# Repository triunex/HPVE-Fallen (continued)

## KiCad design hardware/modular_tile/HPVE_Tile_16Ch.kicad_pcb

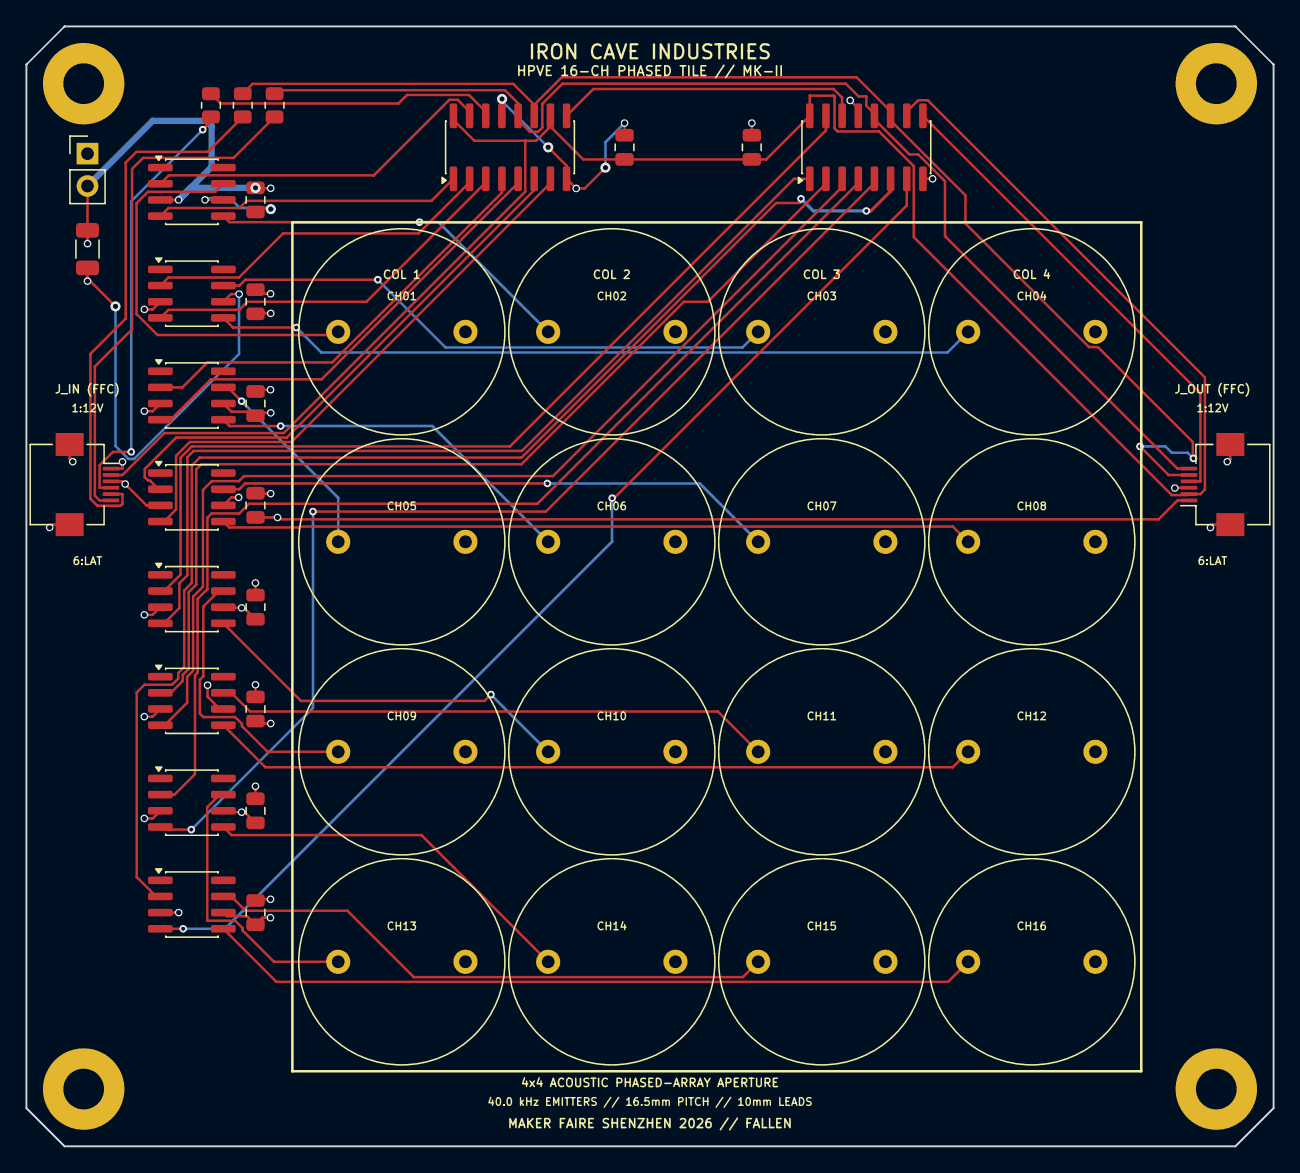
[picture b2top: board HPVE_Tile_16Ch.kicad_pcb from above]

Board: 4 copper layers, 98.0 x 88.0 mm, 47 parts (0 on the bottom side), 43 nets.

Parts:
C1, C2: 0.1uF; C_0805_2012Metric
C101, C102, C103, C104, C105, C106, C107, C108: 0.1uF_50V; C_0805_2012Metric
C_BULK: 10uF_25V; C_1206_3216Metric
H1, H2, H3, H4: M3_Pad; MountingHole_3.2mm_M3_Pad
J_IN: 0.5mm_FFC_6P; Hirose_FH12-6S-0.5SH_1x06-1MP_P0.50mm_Horizontal
J_OUT: 0.5mm_FFC_6P; Hirose_FH12-6S-0.5SH_1x06-1MP_P0.50mm_Horizontal
J_PWR: AUX_12V_IN; PinHeader_1x02_P2.54mm_Vertical
R1, R2, R3: 33R; R_0805_2012Metric
TX1, TX2, TX3, TX4, TX5, TX6, TX7, TX8, TX9, TX10, TX11, TX12, TX13, TX14, TX15, TX16: 400ST160_FEMALE_SOCKET; TX_400ST160_P10.0mm
U1, U2: 74HC595; SOIC-16_3.9x9.9mm_P1.27mm
U101, U102, U103, U104, U105, U106, U107, U108: TC4427ACOA; SOIC-8_3.9x4.9mm_P1.27mm

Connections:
+5V: C1.1, C2.1, J_IN.2, J_OUT.2, U1.10, U1.16, U2.10, U2.16
+12V: C101.1, C102.1, C103.1, C104.1, C105.1, C106.1, C107.1, C108.1, C_BULK.1, J_IN.1, J_OUT.1, J_PWR.1, U101.6, U102.6, U103.6, U104.6, U105.6, U106.6, U107.6, U108.6
DRV_1: TX1.1, U101.7
DRV_2: TX2.1, U101.5
DRV_3: TX3.1, U102.7
DRV_4: TX4.1, U102.5
DRV_5: TX5.1, U103.7
DRV_6: TX6.1, U103.5
DRV_7: TX7.1, U104.7
DRV_8: TX8.1, U104.5
DRV_9: TX9.1, U105.7
DRV_10: TX10.1, U105.5
DRV_11: TX11.1, U106.7
DRV_12: TX12.1, U106.5
DRV_13: TX13.1, U107.7
DRV_14: TX14.1, U107.5
DRV_15: TX15.1, U108.7
DRV_16: TX16.1, U108.5
GND: C1.2, C2.2, C101.2, C102.2, C103.2, C104.2, C105.2, C106.2, C107.2, C108.2, C_BULK.2, H1.1, H2.1, H3.1, H4.1, J_IN.3, J_IN.MP, J_OUT.3, J_OUT.MP, J_PWR.2, TX1.2, TX2.2, TX3.2, TX4.2, TX5.2, TX6.2, TX7.2, TX8.2, TX9.2, TX10.2, TX11.2, TX12.2, TX13.2, TX14.2, TX15.2, TX16.2, U1.8, U1.13, U2.8, U2.13, U101.3, U102.3, U103.3, U104.3, U105.3, U106.3, U107.3, U108.3
SIG_1: U1.15, U101.2
SIG_2: U1.1, U101.4
SIG_3: U1.2, U102.2
SIG_4: U1.3, U102.4
SIG_5: U1.4, U103.2
SIG_6: U1.5, U103.4
SIG_7: U1.6, U104.2
SIG_8: U1.7, U104.4
SIG_9: U2.15, U105.2
SIG_10: U2.1, U105.4
SIG_11: U2.2, U106.2
SIG_12: U2.3, U106.4
SIG_13: U2.4, U107.2
SIG_14: U2.5, U107.4
SIG_15: U2.6, U108.2
SIG_16: U2.7, U108.4
SPI_LATCH: J_OUT.6, R3.2, U1.12, U2.12
SPI_LATCH_IN: J_IN.6, R3.1
SPI_MOSI: R1.2, U1.14
SPI_MOSI_CASCADE: U1.9, U2.14
SPI_MOSI_IN: J_IN.4, R1.1
SPI_MOSI_OUT: J_OUT.4, U2.9
SPI_SCK: J_OUT.5, R2.2, U1.11, U2.11
SPI_SCK_IN: J_IN.5, R2.1

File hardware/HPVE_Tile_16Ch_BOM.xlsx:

Comment | Designator | Footprint | LCSC Part #
74HC595D SOIC-16 Shift Register | U1,U2 | SOIC-16_3.9x9.9mm_P1.27mm | C5947
TC4427EOA SOIC-8 Dual Driver | U101,U102,U103,U104,U105,U106,U107,U108 | SOIC-8_3.9x4.9mm_P1.27mm | C636891
0.1uF 50V X7R Ceramic 0805 | C1,C2 | C_0805_2012Metric | C49678
0.1uF 50V X7R Ceramic 0805 | C101,C102,C103,C104,C105,C106,C107,C108 | C_0805_2012Metric | C49678
10uF 25V X7R Ceramic MLCC 1206 | C_BULK | C_1206_3216Metric | C15850
33R 1% 0805 Resistor | R1,R2,R3 | R_0805_2012Metric | C17631
0.5mm FFC 6-Pin Horizontal Connector | J_IN,J_OUT | Hirose_FH12-6S-0.5SH_1x06-1MP_P0.50mm_Horizontal
400ST160 Transducer Female Socket 1x02 | TX1,TX2,TX3,TX4,TX5,TX6,TX7,TX8,TX9,TX10,TX11,TX12,TX13,TX14,TX15,TX16 | PinSocket_1x02_P2.54mm_Vertical
AUX 12V/GND Header 1x02 P2.54mm | J_PWR | PinHeader_1x02_P2.54mm_Vertical

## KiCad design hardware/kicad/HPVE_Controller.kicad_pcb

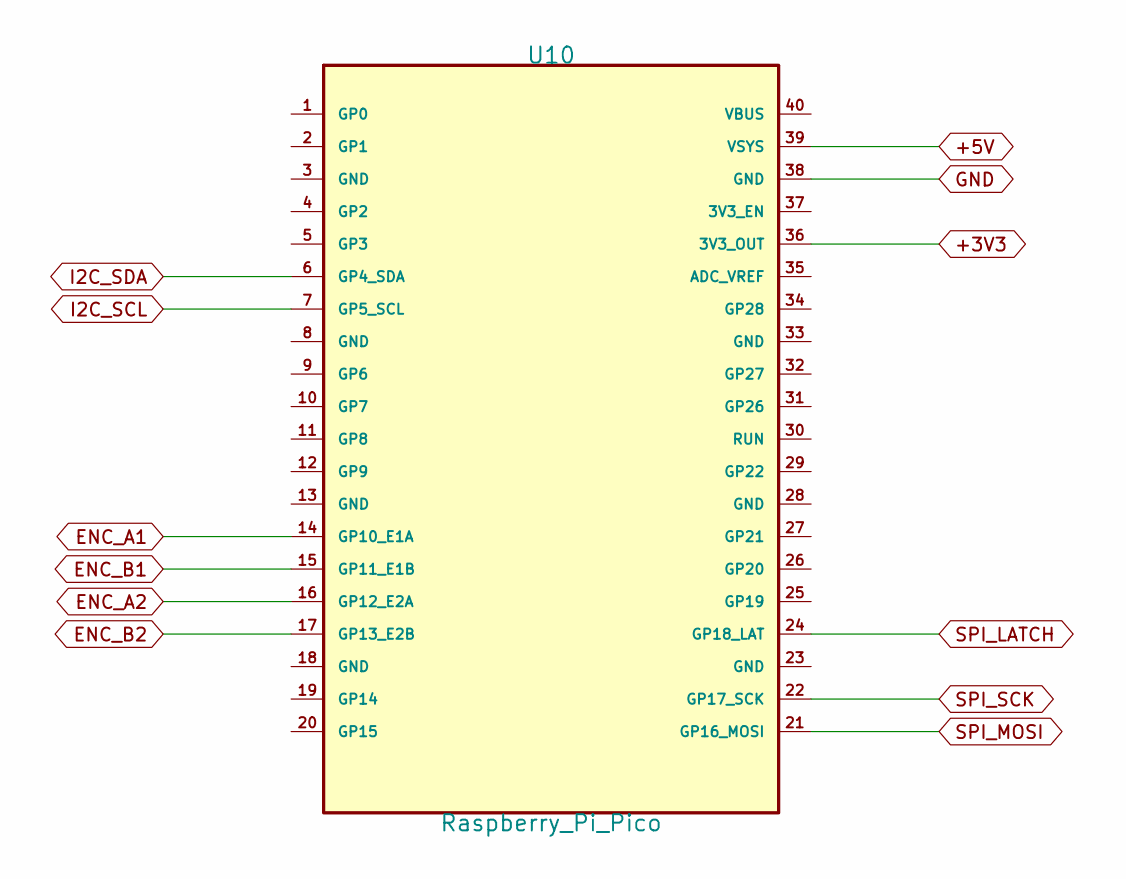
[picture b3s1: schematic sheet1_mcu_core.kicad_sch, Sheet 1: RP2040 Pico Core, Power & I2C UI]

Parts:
U10: Raspberry_Pi_Pico; PinHeader_2x20_P2.54mm_Vertical

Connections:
/RP2040_Core_UI/+5V: U10.39 (VSYS)
/RP2040_Core_UI/SPI_MOSI: U10.36 (3V3_OUT)
GND: U10.38 (GND); also elsewhere on the board
SPI_LATCH: U10.24 (GP18_LAT); also elsewhere on the board
SPI_MOSI: U10.21 (GP16_MOSI); also elsewhere on the board
SPI_SCK: U10.22 (GP17_SCK); also elsewhere on the board

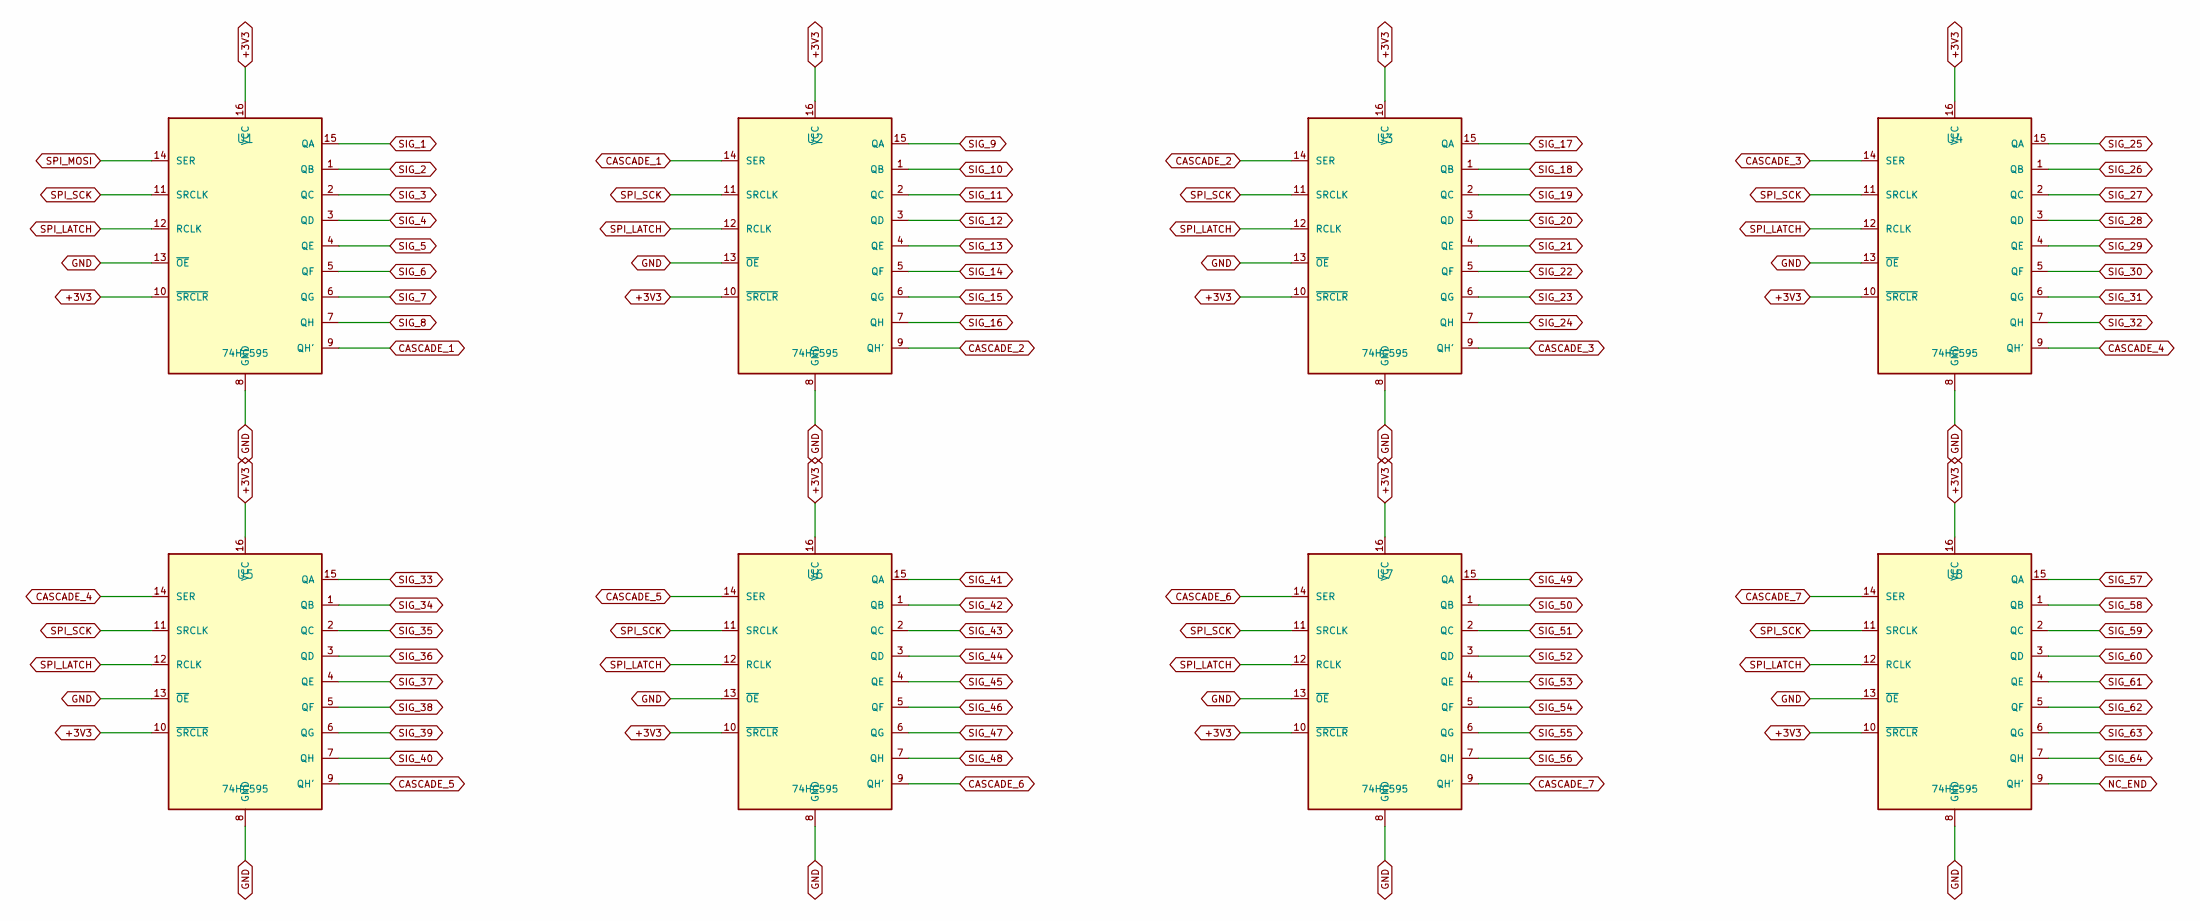
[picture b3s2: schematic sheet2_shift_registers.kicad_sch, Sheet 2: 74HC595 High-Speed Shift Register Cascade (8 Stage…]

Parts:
U1, U2, U3, U4, U5, U6, U7, U8: 74HC595; DIP-16_W7.62mm

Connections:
/Shift_Register_Cascade/SPI_SCK: U1.8 (GND), U1.13 (~OE), U2.8 (GND), U2.13 (~OE), U3.8 (GND), U3.13 (~OE), U4.8 (GND), U4.13 (~OE), U5.8 (GND), U5.13 (~OE), U6.8 (GND), U6.13 (~OE), U7.8 (GND), U7.13 (~OE), U8.8 (GND), U8.13 (~OE)
CASCADE_1: U1.9 (QH'), U2.14 (SER)
CASCADE_2: U2.9 (QH'), U3.14 (SER)
CASCADE_3: U3.9 (QH'), U4.14 (SER)
CASCADE_4: U4.9 (QH'), U5.14 (SER)
CASCADE_5: U5.9 (QH'), U6.14 (SER)
CASCADE_6: U6.9 (QH'), U7.14 (SER)
CASCADE_7: U7.9 (QH'), U8.14 (SER)
SIG_1: U1.15 (QA); also elsewhere on the board
SIG_2: U1.1 (QB); also elsewhere on the board
SIG_3: U1.2 (QC); also elsewhere on the board
SIG_4: U1.3 (QD); also elsewhere on the board
SIG_5: U1.4 (QE); also elsewhere on the board
SIG_6: U1.5 (QF); also elsewhere on the board
SIG_7: U1.6 (QG); also elsewhere on the board
SIG_8: U1.7 (QH); also elsewhere on the board
SIG_9: U2.15 (QA); also elsewhere on the board
SIG_10: U2.1 (QB); also elsewhere on the board
SIG_11: U2.2 (QC); also elsewhere on the board
SIG_12: U2.3 (QD); also elsewhere on the board
SIG_13: U2.4 (QE); also elsewhere on the board
SIG_14: U2.5 (QF); also elsewhere on the board
SIG_15: U2.6 (QG); also elsewhere on the board
SIG_16: U2.7 (QH); also elsewhere on the board
SIG_17: U3.15 (QA); also elsewhere on the board
SIG_18: U3.1 (QB); also elsewhere on the board
SIG_19: U3.2 (QC); also elsewhere on the board
SIG_20: U3.3 (QD); also elsewhere on the board
SIG_21: U3.4 (QE); also elsewhere on the board
SIG_22: U3.5 (QF); also elsewhere on the board
SIG_23: U3.6 (QG); also elsewhere on the board
SIG_24: U3.7 (QH); also elsewhere on the board
SIG_25: U4.15 (QA); also elsewhere on the board
SIG_26: U4.1 (QB); also elsewhere on the board
SIG_27: U4.2 (QC); also elsewhere on the board
SIG_28: U4.3 (QD); also elsewhere on the board
SIG_29: U4.4 (QE); also elsewhere on the board
SIG_30: U4.5 (QF); also elsewhere on the board
SIG_31: U4.6 (QG); also elsewhere on the board
SIG_32: U4.7 (QH); also elsewhere on the board
SIG_33: U5.15 (QA); also elsewhere on the board
SIG_34: U5.1 (QB); also elsewhere on the board
SIG_35: U5.2 (QC); also elsewhere on the board
SIG_36: U5.3 (QD); also elsewhere on the board
SIG_37: U5.4 (QE); also elsewhere on the board
SIG_38: U5.5 (QF); also elsewhere on the board
SIG_39: U5.6 (QG); also elsewhere on the board
SIG_40: U5.7 (QH); also elsewhere on the board
SIG_41: U6.15 (QA); also elsewhere on the board
SIG_42: U6.1 (QB); also elsewhere on the board
SIG_43: U6.2 (QC); also elsewhere on the board
SIG_44: U6.3 (QD); also elsewhere on the board
SIG_45: U6.4 (QE); also elsewhere on the board
SIG_46: U6.5 (QF); also elsewhere on the board
SIG_47: U6.6 (QG); also elsewhere on the board
SIG_48: U6.7 (QH); also elsewhere on the board
SIG_49: U7.15 (QA); also elsewhere on the board
SIG_50: U7.1 (QB); also elsewhere on the board
SIG_51: U7.2 (QC); also elsewhere on the board
SIG_52: U7.3 (QD); also elsewhere on the board
SIG_53: U7.4 (QE); also elsewhere on the board
SIG_54: U7.5 (QF); also elsewhere on the board
SIG_55: U7.6 (QG); also elsewhere on the board
SIG_56: U7.7 (QH); also elsewhere on the board
SIG_57: U8.15 (QA); also elsewhere on the board
SIG_58: U8.1 (QB); also elsewhere on the board
SIG_59: U8.2 (QC); also elsewhere on the board
SIG_60: U8.3 (QD); also elsewhere on the board
SIG_61: U8.4 (QE); also elsewhere on the board
SIG_62: U8.5 (QF); also elsewhere on the board
SIG_63: U8.6 (QG); also elsewhere on the board
SIG_64: U8.7 (QH); also elsewhere on the board
SPI_LATCH: U1.12 (RCLK), U2.12 (RCLK), U3.12 (RCLK), U4.12 (RCLK), U5.12 (RCLK), U6.12 (RCLK), U7.12 (RCLK), U8.12 (RCLK); also elsewhere on the board
SPI_MOSI: U1.14 (SER); also elsewhere on the board
SPI_SCK: U1.11 (SRCLK), U2.11 (SRCLK), U3.11 (SRCLK), U4.11 (SRCLK), U5.11 (SRCLK), U6.11 (SRCLK), U7.11 (SRCLK), U8.11 (SRCLK); also elsewhere on the board

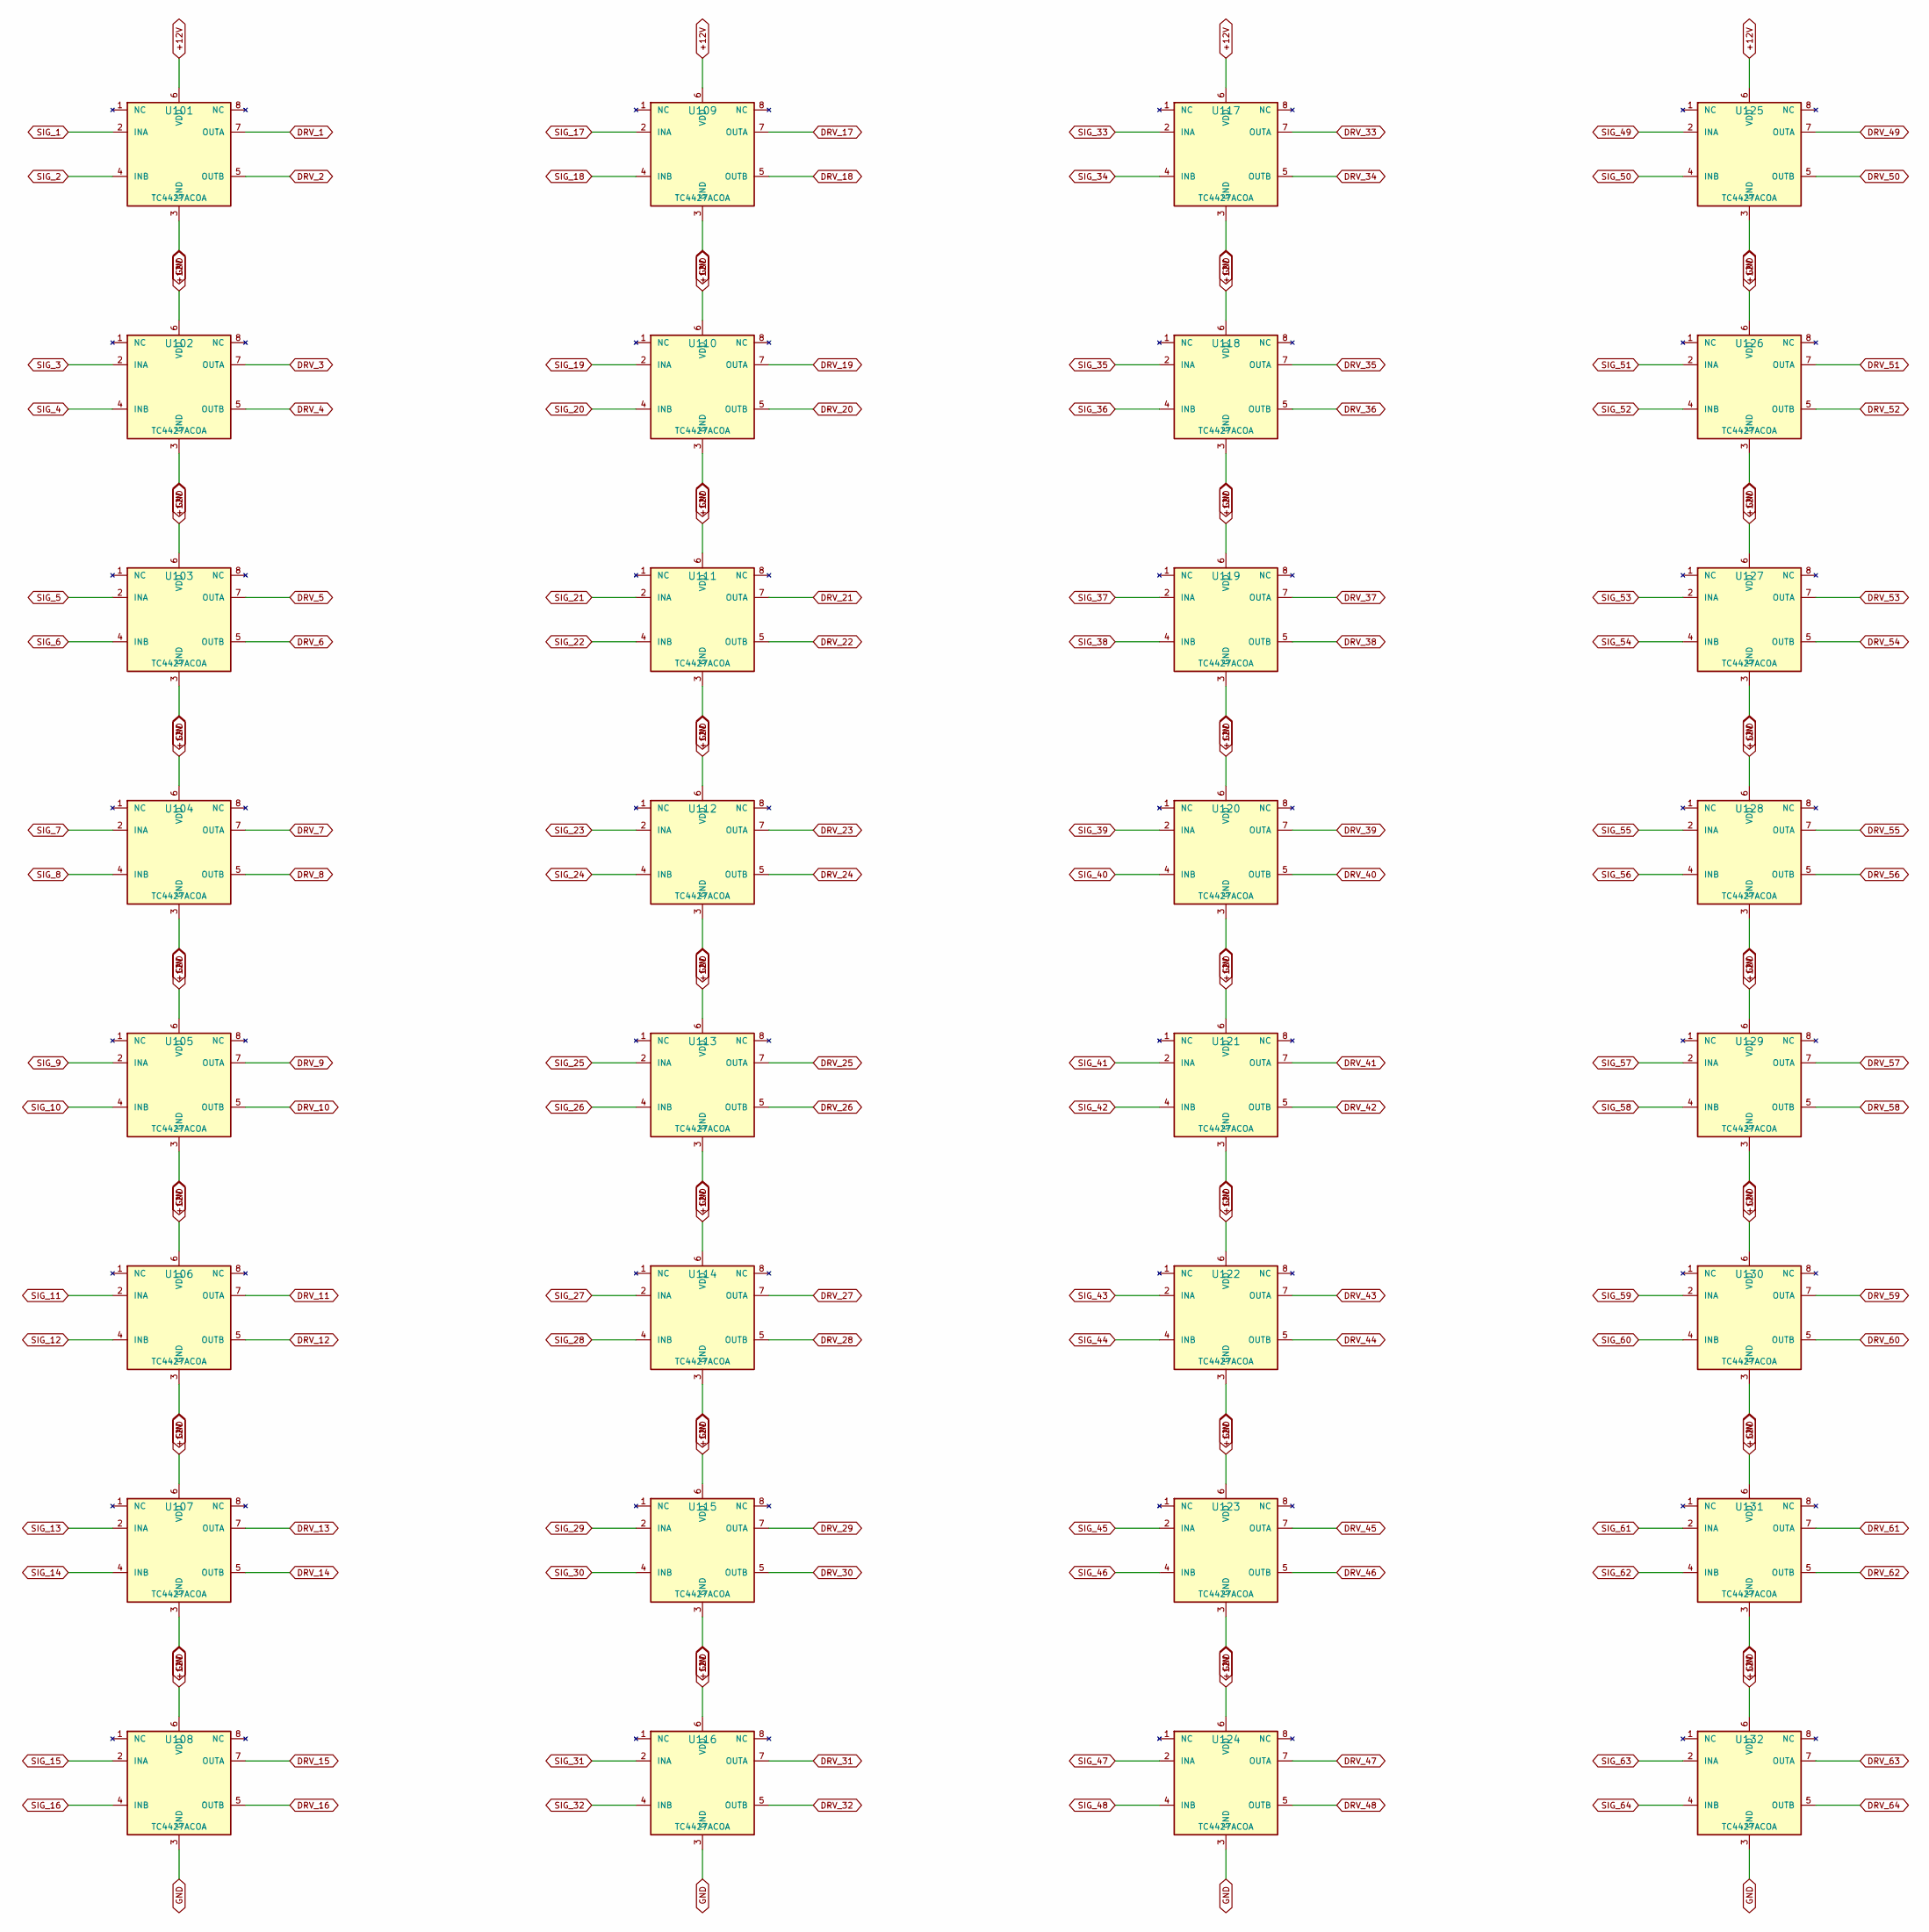
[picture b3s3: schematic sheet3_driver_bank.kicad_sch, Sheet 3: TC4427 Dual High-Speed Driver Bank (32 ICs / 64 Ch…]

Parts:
U101, U102, U103, U104, U105, U106, U107, U108, U109, U110, U111, U112, U113, U114, U115, U116, U117, U118, U119, U120, U121, U122, U123, U124, U125, U126, U127, U128, U129, U130, U131, U132: TC4427ACOA; SOIC-8_3.9x4.9mm_P1.27mm

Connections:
+12V: U101.6 (VDD), U102.6 (VDD), U103.6 (VDD), U104.6 (VDD), U105.6 (VDD), U106.6 (VDD), U107.6 (VDD), U108.6 (VDD), U109.6 (VDD), U110.6 (VDD), U111.6 (VDD), U112.6 (VDD), U113.6 (VDD), U114.6 (VDD), U115.6 (VDD), U116.6 (VDD), U117.6 (VDD), U118.6 (VDD), U119.6 (VDD), U120.6 (VDD), U121.6 (VDD), U122.6 (VDD), U123.6 (VDD), U124.6 (VDD), U125.6 (VDD), U126.6 (VDD), U127.6 (VDD), U128.6 (VDD), U129.6 (VDD), U130.6 (VDD), U131.6 (VDD), U132.6 (VDD)
/TC4427_Driver_Bank/GND: U101.3 (GND), U102.3 (GND), U103.3 (GND), U104.3 (GND), U105.3 (GND), U106.3 (GND), U107.3 (GND), U108.3 (GND), U109.3 (GND), U110.3 (GND), U111.3 (GND), U112.3 (GND), U113.3 (GND), U114.3 (GND), U115.3 (GND), U116.3 (GND), U117.3 (GND), U118.3 (GND), U119.3 (GND), U120.3 (GND), U121.3 (GND), U122.3 (GND), U123.3 (GND), U124.3 (GND), U125.3 (GND), U126.3 (GND), U127.3 (GND), U128.3 (GND), U129.3 (GND), U130.3 (GND), U131.3 (GND), U132.3 (GND)
DRV_1: U101.7 (OUTA); also elsewhere on the board
DRV_2: U101.5 (OUTB); also elsewhere on the board
DRV_3: U102.7 (OUTA); also elsewhere on the board
DRV_4: U102.5 (OUTB); also elsewhere on the board
DRV_5: U103.7 (OUTA); also elsewhere on the board
DRV_6: U103.5 (OUTB); also elsewhere on the board
DRV_7: U104.7 (OUTA); also elsewhere on the board
DRV_8: U104.5 (OUTB); also elsewhere on the board
DRV_9: U105.7 (OUTA); also elsewhere on the board
DRV_10: U105.5 (OUTB); also elsewhere on the board
DRV_11: U106.7 (OUTA); also elsewhere on the board
DRV_12: U106.5 (OUTB); also elsewhere on the board
DRV_13: U107.7 (OUTA); also elsewhere on the board
DRV_14: U107.5 (OUTB); also elsewhere on the board
DRV_15: U108.7 (OUTA); also elsewhere on the board
DRV_16: U108.5 (OUTB); also elsewhere on the board
DRV_17: U109.7 (OUTA); also elsewhere on the board
DRV_18: U109.5 (OUTB); also elsewhere on the board
DRV_19: U110.7 (OUTA); also elsewhere on the board
DRV_20: U110.5 (OUTB); also elsewhere on the board
DRV_21: U111.7 (OUTA); also elsewhere on the board
DRV_22: U111.5 (OUTB); also elsewhere on the board
DRV_23: U112.7 (OUTA); also elsewhere on the board
DRV_24: U112.5 (OUTB); also elsewhere on the board
DRV_25: U113.7 (OUTA); also elsewhere on the board
DRV_26: U113.5 (OUTB); also elsewhere on the board
DRV_27: U114.7 (OUTA); also elsewhere on the board
DRV_28: U114.5 (OUTB); also elsewhere on the board
DRV_29: U115.7 (OUTA); also elsewhere on the board
DRV_30: U115.5 (OUTB); also elsewhere on the board
DRV_31: U116.7 (OUTA); also elsewhere on the board
DRV_32: U116.5 (OUTB); also elsewhere on the board
DRV_33: U117.7 (OUTA); also elsewhere on the board
DRV_34: U117.5 (OUTB); also elsewhere on the board
DRV_35: U118.7 (OUTA); also elsewhere on the board
DRV_36: U118.5 (OUTB); also elsewhere on the board
DRV_37: U119.7 (OUTA); also elsewhere on the board
DRV_38: U119.5 (OUTB); also elsewhere on the board
DRV_39: U120.7 (OUTA); also elsewhere on the board
DRV_40: U120.5 (OUTB); also elsewhere on the board
DRV_41: U121.7 (OUTA); also elsewhere on the board
DRV_42: U121.5 (OUTB); also elsewhere on the board
DRV_43: U122.7 (OUTA); also elsewhere on the board
DRV_44: U122.5 (OUTB); also elsewhere on the board
DRV_45: U123.7 (OUTA); also elsewhere on the board
DRV_46: U123.5 (OUTB); also elsewhere on the board
DRV_47: U124.7 (OUTA); also elsewhere on the board
DRV_48: U124.5 (OUTB); also elsewhere on the board
DRV_49: U125.7 (OUTA); also elsewhere on the board
DRV_50: U125.5 (OUTB); also elsewhere on the board
DRV_51: U126.7 (OUTA); also elsewhere on the board
DRV_52: U126.5 (OUTB); also elsewhere on the board
DRV_53: U127.7 (OUTA); also elsewhere on the board
DRV_54: U127.5 (OUTB); also elsewhere on the board
DRV_55: U128.7 (OUTA); also elsewhere on the board
DRV_56: U128.5 (OUTB); also elsewhere on the board
DRV_57: U129.7 (OUTA); also elsewhere on the board
DRV_58: U129.5 (OUTB); also elsewhere on the board
DRV_59: U130.7 (OUTA); also elsewhere on the board
DRV_60: U130.5 (OUTB); also elsewhere on the board
DRV_61: U131.7 (OUTA); also elsewhere on the board
DRV_62: U131.5 (OUTB); also elsewhere on the board
DRV_63: U132.7 (OUTA); also elsewhere on the board
DRV_64: U132.5 (OUTB); also elsewhere on the board
SIG_1: U101.2 (INA); also elsewhere on the board
SIG_2: U101.4 (INB); also elsewhere on the board
SIG_3: U102.2 (INA); also elsewhere on the board
SIG_4: U102.4 (INB); also elsewhere on the board
SIG_5: U103.2 (INA); also elsewhere on the board
SIG_6: U103.4 (INB); also elsewhere on the board
SIG_7: U104.2 (INA); also elsewhere on the board
SIG_8: U104.4 (INB); also elsewhere on the board
SIG_9: U105.2 (INA); also elsewhere on the board
SIG_10: U105.4 (INB); also elsewhere on the board
SIG_11: U106.2 (INA); also elsewhere on the board
SIG_12: U106.4 (INB); also elsewhere on the board
SIG_13: U107.2 (INA); also elsewhere on the board
SIG_14: U107.4 (INB); also elsewhere on the board
SIG_15: U108.2 (INA); also elsewhere on the board
SIG_16: U108.4 (INB); also elsewhere on the board
SIG_17: U109.2 (INA); also elsewhere on the board
SIG_18: U109.4 (INB); also elsewhere on the board
SIG_19: U110.2 (INA); also elsewhere on the board
SIG_20: U110.4 (INB); also elsewhere on the board
SIG_21: U111.2 (INA); also elsewhere on the board
SIG_22: U111.4 (INB); also elsewhere on the board
SIG_23: U112.2 (INA); also elsewhere on the board
SIG_24: U112.4 (INB); also elsewhere on the board
SIG_25: U113.2 (INA); also elsewhere on the board
SIG_26: U113.4 (INB); also elsewhere on the board
SIG_27: U114.2 (INA); also elsewhere on the board
SIG_28: U114.4 (INB); also elsewhere on the board
SIG_29: U115.2 (INA); also elsewhere on the board
SIG_30: U115.4 (INB); also elsewhere on the board
SIG_31: U116.2 (INA); also elsewhere on the board
SIG_32: U116.4 (INB); also elsewhere on the board
SIG_33: U117.2 (INA); also elsewhere on the board
SIG_34: U117.4 (INB); also elsewhere on the board
SIG_35: U118.2 (INA); also elsewhere on the board
SIG_36: U118.4 (INB); also elsewhere on the board
SIG_37: U119.2 (INA); also elsewhere on the board
SIG_38: U119.4 (INB); also elsewhere on the board
SIG_39: U120.2 (INA); also elsewhere on the board
SIG_40: U120.4 (INB); also elsewhere on the board
SIG_41: U121.2 (INA); also elsewhere on the board
SIG_42: U121.4 (INB); also elsewhere on the board
SIG_43: U122.2 (INA); also elsewhere on the board
SIG_44: U122.4 (INB); also elsewhere on the board
SIG_45: U123.2 (INA); also elsewhere on the board
SIG_46: U123.4 (INB); also elsewhere on the board
SIG_47: U124.2 (INA); also elsewhere on the board
SIG_48: U124.4 (INB); also elsewhere on the board
SIG_49: U125.2 (INA); also elsewhere on the board
SIG_50: U125.4 (INB); also elsewhere on the board
SIG_51: U126.2 (INA); also elsewhere on the board
SIG_52: U126.4 (INB); also elsewhere on the board
SIG_53: U127.2 (INA); also elsewhere on the board
SIG_54: U127.4 (INB); also elsewhere on the board
SIG_55: U128.2 (INA); also elsewhere on the board
SIG_56: U128.4 (INB); also elsewhere on the board
SIG_57: U129.2 (INA); also elsewhere on the board
SIG_58: U129.4 (INB); also elsewhere on the board
SIG_59: U130.2 (INA); also elsewhere on the board
SIG_60: U130.4 (INB); also elsewhere on the board
SIG_61: U131.2 (INA); also elsewhere on the board
SIG_62: U131.4 (INB); also elsewhere on the board
SIG_63: U132.2 (INA); also elsewhere on the board
SIG_64: U132.4 (INB); also elsewhere on the board
